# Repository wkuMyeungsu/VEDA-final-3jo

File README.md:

# 지게차 사각지대 충돌 방지 통합 안전 시스템

한화비전 VEDA 프로그램 3조 팀 프로젝트 — CCTV 영상 분석 및 센서 융합을 통해 지게차 사각지대의 보행자를 감지하고 충돌을 방지하는 시스템입니다.

---

## 🌐 1. 물리 장비 배포 아키텍처

각 소프트웨어는 물리적으로 분리된 4개의 독립 하드웨어에서 구동되며 네트워크로 연동됩니다:

```text
       ┌────────────────────────────────┐
       │   📹 CCTV (한화비전 네트워크)     │
       │   - 4채널 영상 및 AI 검출 메타데이터  │
       │   - IP: 192.168.0.3            │
       └──────────────┬─────────────────┘
                      │ RTSP (포트 554)
                      ▼
       ┌────────────────────────────────┐
       │  🍓 중앙 안전 서버 (라즈베리파이 #1)  │
       │  - server/ (C++ 안전 판정 서버)   │
       │  - IP: 192.168.0.13 (MQTT TLS 8883)│
       └──────┬─────────────────┬───────┘
              │ MQTT (위험 이벤트) │ MQTT (관제 데이터)
              ▼                 ▼
┌───────────────────────────┐  ┌───────────────────────────┐
│ 🚜 지게차 운전자 단말     │  │ 🖥️ 중앙 관제 센터        │
│ (라즈베리파이 #2 + FPGA)   │  │ (관제 PC / Windows)       │
│ - forklift-device/        │  │ - operator-device/        │
│ - 운전자 터치 UI & 경광등  │  │ - 3단계 계층 관제 화면    │
└───────────────────────────┘  └───────────────────────────┘
```

---

## 🏛️ 2. 하드웨어별 역할 및 배포 대상

| 디렉터리 | 배포 대상 기기 | 담당 역할 | 기술 스택 | 세부 가이드 |
|---|---|---|---|:---:|
| [`forklift-device/`](forklift-device/README.md) | **지게차 단말** (라즈베리파이 #2 + FPGA) | 운전자 터치 UI, 4채널 영상, 위험 경고 배너, FPGA 경광등/부저 제어 | Qt 6 / QML, C++17, Verilog | [바로가기](forklift-device/README.md) |
| [`operator-device/`](operator-device/README.md) | **관제실 PC** (Windows 10/11) | 3단계 계층 탐색(구역→카메라→4채널), 실시간 모니터링, 일일 안전일지 CSV 관리 | Qt 6 / QML, C++17 | [바로가기](operator-device/README.md) |
| [`server/`](server/README.md) | **중앙 서버** (라즈베리파이 #1) | CCTV/센서 메타데이터 수신, 호모그래피 좌표 변환, 위험도 계산, MQTT 브로드캐스트 | C++17, Python, SQLite | [바로가기](server/README.md) |
| [`cctv/`](cctv/ArUCoDetector/README.md) | **현장 CCTV** (카메라 내부) | ArUco 마커 검출, 렌즈 왜곡 보정 및 메타데이터 전송 | C++, OpenCV, OpenSDK | [바로가기](cctv/ArUCoDetector/README.md) |

---

## 🚀 3. 장비별 빠른 실행 가이드 (Quick Start)

### 🚜 1) 지게차 운전자 단말 (라즈베리파이 환경 / Linux)
- **작업 경로**: `~/VEDA_Final_project` (저장소 루트)
```bash
# 원클릭 빌드
./build_forklift.sh

# 데모 실행 (Mock 영상 및 이벤트)
./run_forklift.sh --demo --camera CAM_01_CH_01
```
> 실행 후 키보드 `Ctrl + Shift + D`로 데모 조작 패널을 열 수 있습니다. (산출물: `forklift-device/qt/build/operator_terminal`)

---

### 🖥️ 2) 중앙 관제 센터 (관제실 PC / Windows MinGW)
- **작업 경로**: `C:\VEDA_Final_project` (저장소 루트)
```powershell
# 원클릭 빌드
.\build_operator.bat

# 데모 실행
.\run_operator.bat
```
> 로그인: ID `hanwha` / PIN `5hanwha!` (로그인 후 `Ctrl + Shift + D`로 데모 패널 열기)  
> (산출물: `operator-device\qt\build\windows-mingw\control_center.exe`)

---

### 💻 3) 지게차 단말 Windows PC 개발/테스트용 실행
- **작업 경로**: `C:\VEDA_Final_project`
```powershell
.\build_forklift.bat
.\run_forklift.bat
```

> 💡 **PowerShell 단축어**: `. .\setup_aliases.ps1` 실행 시 `bo`(관제 빌드), `ro`(관제 실행), `bf`(단말 빌드), `rf`(단말 실행) 사용 가능

---

## 📖 트랙별 메인 가이드
- **지게차 운전자 단말**: [`forklift-device/README.md`](forklift-device/README.md)
- **중앙 관제 센터**: [`operator-device/README.md`](operator-device/README.md)
- **중앙 안전 서버**: [`server/README.md`](server/README.md)
- **현장 CCTV (ArUco)**: [`cctv/ArUCoDetector/README.md`](cctv/ArUCoDetector/README.md)

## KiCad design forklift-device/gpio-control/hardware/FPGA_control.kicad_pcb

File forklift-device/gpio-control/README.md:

# 🛡️ FPGA 안전 제어기 (gpio-control)

지게차 전자 단말(Pi)이 죽거나 통신이 끊겨도 **경고 표시(LED/부저/7세그)와 전진 차단만큼은
하드웨어로 계속 보장**하는 것을 목표로 하는 최종 안전 방어선입니다. Gowin `GW1NSR-4C`
(GW1NSR-LV4CQN48PC6/I5) FPGA에 Verilog RTL로 구현했습니다.

FPGA는 위험도를 "계산"하지 않습니다 — 계산은 서버가 하고, FPGA는 그 결과를 받아
**우선순위 판단 + 타이밍 제어 + 물리 출력**만 담당합니다.

---

## 📂 디렉터리 구조

```text
gpio-control/
├── src/                        # Verilog RTL + 테스트벤치 + 프로토콜 문서
│   ├── top.v                   # 최상위 모듈 (전체 배선)
│   ├── packet_parser.v         # UART 4바이트 명령 프레임 파싱 + 체크섬 검증
│   ├── warning_fsm.v           # 6단계 우선순위 상태 머신 (SAFE~ESTOP)
│   ├── watchdog.v              # 500ms Pi 통신 두절 감지
│   ├── warning_latch.v         # 위험도 상승 즉시 / 하강 2000ms 지연
│   ├── estop_latch.v           # 비상정지 래치 (무제한, 수동 리셋 전까지)
│   ├── movement_cutoff_latch.v # 전진 차단 릴레이 래치
│   ├── event_detector.v        # 상태 변화 → 이벤트 코드 생성
│   ├── event_tx_fifo.v         # 8-depth 이벤트 전송 큐
│   ├── event_uart_tx.v         # 5바이트 push 프레임 조립
│   ├── heartbeat_gen.v         # 200ms 주기 상태 요약 heartbeat
│   ├── led_pattern.v / buzzer_ctrl.v / self_test_controller.v
│   ├── uart_rx.v / uart_tx.v
│   ├── tb_*.v                  # 테스트벤치 (tb_cutoff, tb_top, tb_post)
│   ├── PROTOCOL.md             # UART 프로토콜 규격서 (필독)
│   └── uart_rx.cst             # 핀 배치 제약 파일
├── hardware/                   # KiCad 프로젝트 (회로도 + PCB)
├── docs/                       # 아키텍처 다이어그램, 회로도/PCB PDF·이미지
├── wireless_relay/             # nRF24L01 + STM32 무선 릴레이 확장
│   ├── PROTOCOL_WIRELESS.md
│   ├── common/                 # 양쪽 보드 공용 (nRF24L01 드라이버, 프레임 검증)
│   ├── tx_node/                # FPGA UART 탭 → 무선 송신
│   └── rx_node/                # 무선 수신 → 릴레이 GPIO + 워치독
└── FPGA_control.gprj           # Gowin EDA 프로젝트 파일
```

---

## 🧠 핵심 아키텍처

```
Pi → [uart_rx] → [packet_parser] → risk_level ──▶ warning_latch ──▶ effective_risk ─┐
                                    (checksum 검증)  (상승즉시/하강2000ms)            │
                                                                                      ▼
estop_n ─▶ estop_filter ─▶ estop_latch ──▶ estop_active ───────────────────▶ warning_fsm
                           (manual_reset_n으로 해제)                          (6단계 우선순위)
                                  │                                                  │
                                  └──▶ movement_cutoff_trigger ──▶ movement_cutoff_latch
                                       (estop_active ∥ CRITICAL)      └─▶ fwd_cutoff_relay_en

warning_state → led_pattern / buzzer_ctrl / warning_state_bcd(7세그)

(상태 변화 or 200ms) → event_detector/heartbeat_gen → event_tx_fifo → event_uart_tx → Pi
```

**의도적 설계 포인트**: `movement_cutoff_trigger`는 CRITICAL·ESTOP만 보고 `COMM_ERROR`는
제외했습니다 — 통신 두절만으로는 전진 차단까지 가지 않고 표시(`warning_state`)에만
반영됩니다(팀 결정, `PROTOCOL.md` §3.2).

---

## 📡 통신 프로토콜 요약

자세한 내용은 [`src/PROTOCOL.md`](src/PROTOCOL.md) 참고.

**Pi → FPGA** (4바이트, 3종류): `[0xAA][command][data][checksum]`
| command | 이름 | 주기 |
|---|---|---|
| 0x01 | SET_RISK | 100ms마다 반복 (watchdog 갱신은 이것만 함) |
| 0x02 | CLEAR_ERROR | 필요할 때 1회 |
| 0x03 | SELF_TEST | 필요할 때 1회 |

**FPGA → Pi** (5바이트, push): `[0x55][event_code][event_detail][seq/overflow/cutoff][checksum]`
- heartbeat 200ms 주기 + 상태 변화 이벤트, 요청-응답 없이 FPGA가 스스로 전송
- checksum = XOR(byte0..3)

---

## 🔧 하드웨어

- **FPGA**: Gowin `GW1NSR-4C` (GW1NSR-LV4CQN48PC6/I5)
- **회로도/PCB**: [`hardware/`](hardware/) (KiCad 프로젝트), 내보낸 문서는
  [`docs/FPGA_control_scematic.pdf`](docs/FPGA_control_scematic.pdf),
  [`docs/FPGA_control_pcb_layout.pdf`](docs/FPGA_control_pcb_layout.pdf)
- **물리 출력**: LED ×2, 부저, 7세그(SN74LS47N BCD 디코더), 스위치 ×2(E-Stop/수동리셋)
- **무선 릴레이 확장**: 전진 차단 릴레이를 nRF24L01 + NUCLEO-F401RE ×2로 무선 구간
  확장. 250kbps, 오토재전송 15회, 600ms(heartbeat×3) 워치독 — 링크 끊김·부팅직후 등
  애매한 상황은 전부 안전 쪽(강제 컷오프)으로 수렴. 자세한 내용은
  [`wireless_relay/PROTOCOL_WIRELESS.md`](wireless_relay/PROTOCOL_WIRELESS.md).

---

## ✅ 검증

**시뮬레이션**: `src/tb_cutoff.v`을 Icarus Verilog로 실행해 6개 시나리오(SAFE, CRITICAL
래치, SAFE 복귀해도 래치 유지, 2000ms hold-down 이후에도 유지, manual_reset 해제,
700ms watchdog timeout 중 래치 유지)를 실측 검증했습니다.

```bash
iverilog -g2012 -o sim.vvp -s tb_cutoff \
  src/tb_cutoff.v src/top.v src/uart_rx.v src/uart_tx.v src/packet_parser.v \
  src/warning_fsm.v src/watchdog.v src/warning_latch.v src/estop_filter.v \
  src/estop_latch.v src/movement_cutoff_latch.v src/led_pattern.v \
  src/buzzer_ctrl.v src/event_detector.v src/event_tx_fifo.v src/event_uart_tx.v \
  src/self_test_controller.v src/heartbeat_gen.v src/button_debounce.v
vvp sim.vvp
```

**합성/배치·배선 (Gowin P&R)**: LUT 999/4,608(22%), Register(FF) 591/3,573(17%),
Setup/Hold 위반 0건(1,658개 경로 분석). ⚠️ 클럭 주파수를 명시적으로 제약하지 않아
Gowin이 기본값(50MHz)으로 분석한 결과이며, 실제 보드 클럭(27MHz, `top.v`
`CLK_FREQ_HZ` 기본값)보다 훨씬 빠른 조건이라 실사용 여유는 충분하지만, 엄밀한
검증을 위해서는 `.cst`에 27MHz 기준 `create_clock` 제약을 추가하는 것을 권장합니다.

---

## 🛠️ 빌드

Gowin EDA(V1.9.11.03 Education 이상)에서 `FPGA_control.gprj` 열기 → Synthesize →
Place & Route → Program Device.

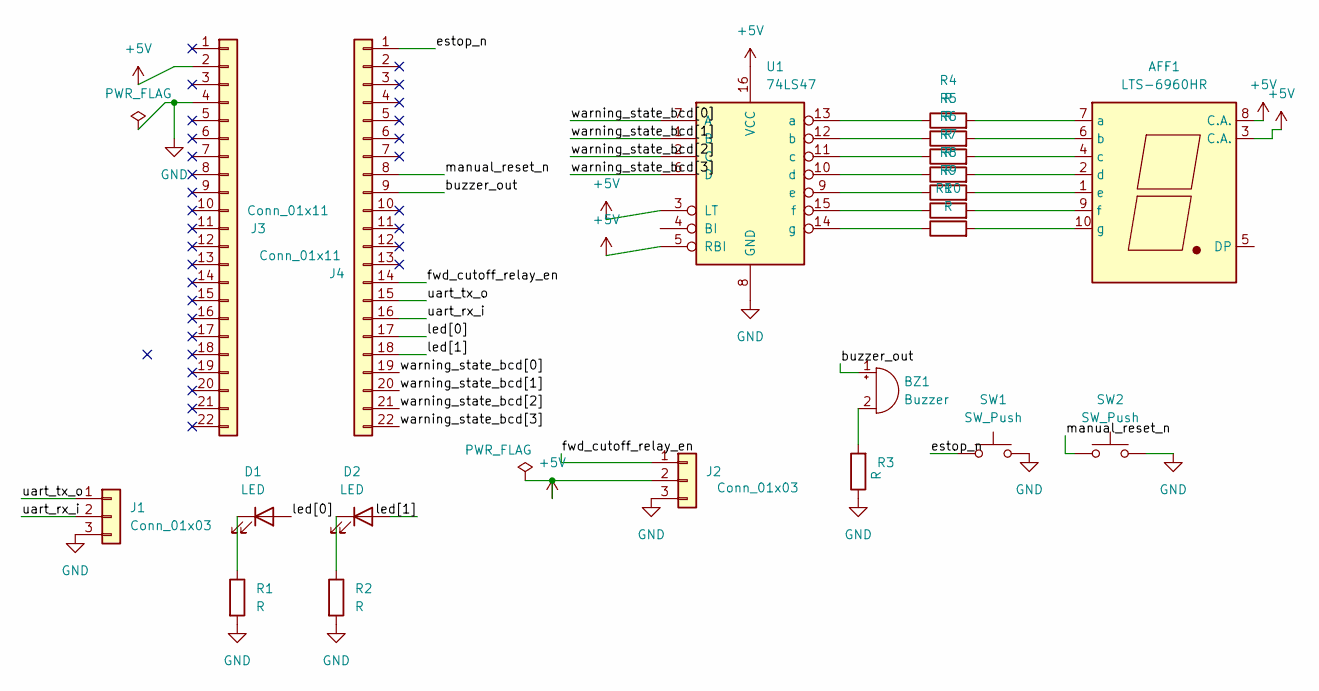
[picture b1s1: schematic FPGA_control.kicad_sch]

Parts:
AFF1: LTS-6960HR; 7SegmentLED_LTS6760_LTS6780
BZ1: Buzzer; Buzzer_12x9.5RM7.6
D1, D2: LED; LED_D8.0mm
J1: Conn_01x03; PinHeader_1x03_P2.54mm_Vertical
J2: Conn_01x03; TerminalBlock_MaiXu_MX126-5.0-03P_1x03_P5.00mm
J3, J4: Conn_01x11; PinSocket_1x22_P2.54mm_Vertical
R1, R2, R3, R4, R5, R6, R7, R8, R9, R10: R; R_Axial_DIN0207_L6.3mm_D2.5mm_P10.16mm_Horizontal
SW1, SW2: SW_Push; SW_PUSH_6mm
U1: 74LS47; DIP-16_W7.62mm_Socket

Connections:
+5V: AFF1.3 (C.A.), AFF1.8 (C.A.), J2.2, J3.2, U1.3 (LT), U1.5 (RBI), U1.16 (VCC)
/buzzer_out: BZ1.1 (+), J4.9
/estop_n: J4.1, SW1.1
/fwd_cutoff_relay_en: J2.1, J4.14
/led[0]: D1.2 (A), J4.17
/led[1]: D2.2 (A), J4.18
/manual_reset_n: J4.8, SW2.1
/uart_rx_i: J1.2, J4.16
/uart_tx_o: J1.1, J4.15
/warning_state_bcd[0]: J4.19, U1.7 (A)
/warning_state_bcd[1]: J4.20, U1.1 (B)
/warning_state_bcd[2]: J4.21, U1.2 (C)
/warning_state_bcd[3]: J4.22, U1.6 (D)
GND: J1.3, J2.3, J3.4, R1.2, R2.2, R3.1, SW1.2, SW2.2, U1.8 (GND)
unnamed: AFF1.7 (a), R4.2
unnamed: AFF1.6 (b), R5.2
unnamed: AFF1.4 (c), R6.2
unnamed: AFF1.2 (d), R7.2
unnamed: AFF1.1 (e), R8.2
unnamed: AFF1.9 (f), R9.2
unnamed: AFF1.10 (g), R10.2
unnamed: BZ1.2 (-), R3.2
unnamed: D1.1 (K), R1.1
unnamed: D2.1 (K), R2.1
unnamed: R4.1, U1.13 (a)
unnamed: R5.1, U1.12 (b)
unnamed: R6.1, U1.11 (c)
unnamed: R7.1, U1.10 (d)
unnamed: R8.1, U1.9 (e)
unnamed: R9.1, U1.15 (f)
unnamed: R10.1, U1.14 (g)

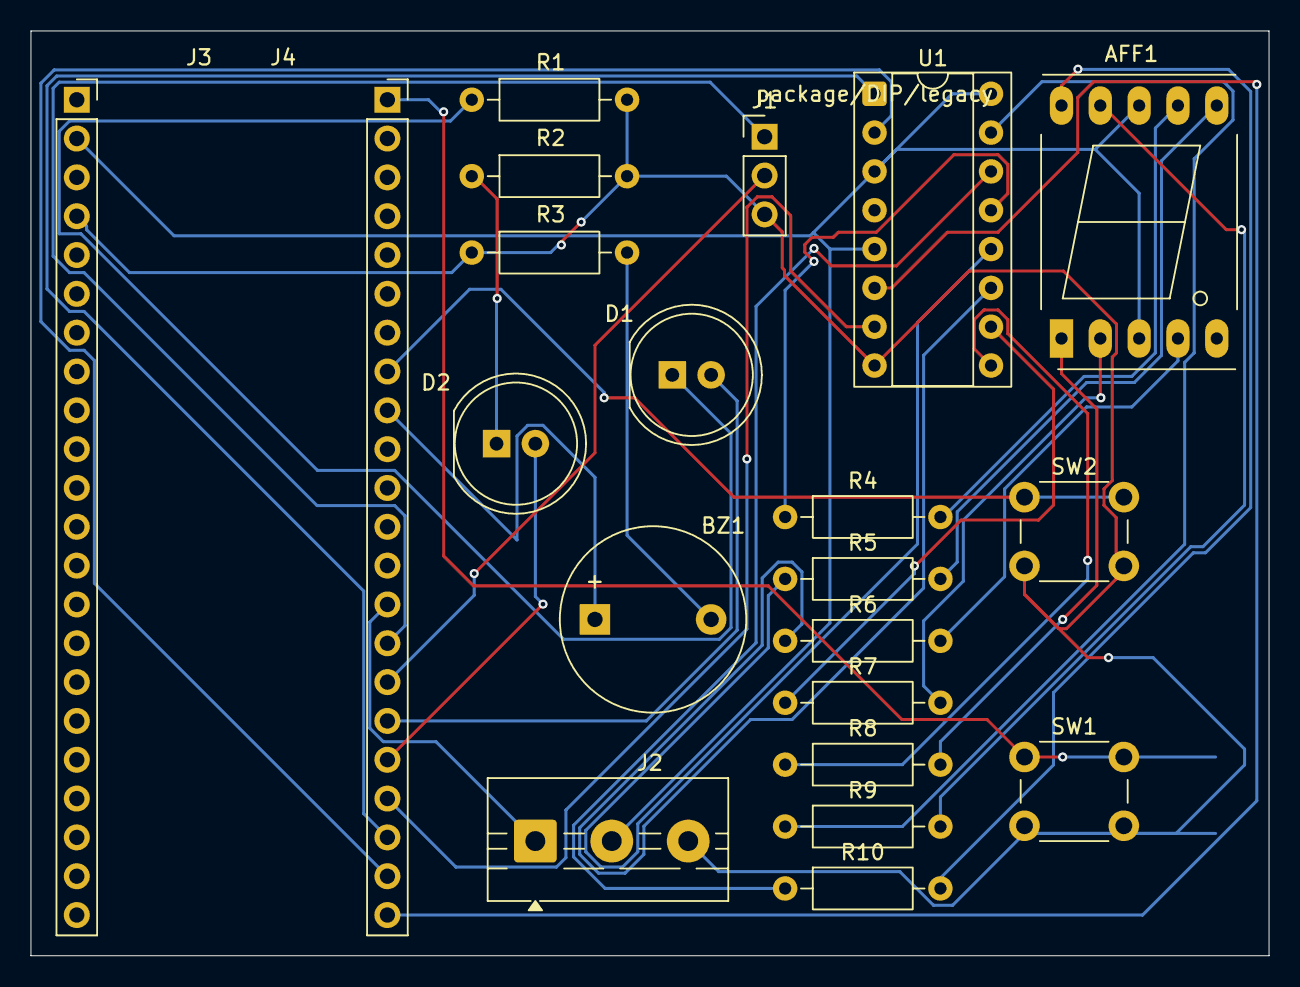
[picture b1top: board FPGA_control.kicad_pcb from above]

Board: 2 copper layers, 81.0 x 60.5 mm, 21 parts (0 on the bottom side), 31 nets.
